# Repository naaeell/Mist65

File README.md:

# Mist65 ⌨✨

Introducing Mist65, a 65% custom keyboard inspired by [bakeneko65](https://github.com/kkatano/bakeneko-65). The PCB, aptly named Mist, features a sleek black design reminiscent of nighttime fog. To keep costs reasonable, the ATmega32u4 controller has been replaced with the budget-friendly RP2040 Zero, maintaining similar functionality.

Designed with a 65% layout, Mist65 strikes a balance between compactness and functionality, housing arrow keys for enhanced usability. VIA support ensures seamless keymap customization to tailor the keyboard to your preferences.

For those interested, the Mist65 PCB is available for purchase [here](https://tokopedia.link/6WUgB6gHmGb) (indonesian domestic). If considering group buy or commercial use, kindly adhere to the specified terms.

For more details about materials, instructions, and other information, please visit this [page](https://github.com/naaeell/Mist65/blob/main/mist65/README.md)

## Features 🔮

- No RGB: Clean and distraction-free experience without RGB lighting.
- Drag and Drop Flashing: Streamlined firmware updates with easy drag-and-drop functionality.
- Staggered Design: Comfortable and ergonomic typing experience with a staggered key layout.
- VIA Support: Extensive keymap customization through VIA support. (Keyboard definition required until VIA branch merge)
- QMK Firmware: Reliable and customizable keyboard experience powered by QMK firmware.
- Cost-Effective Components: Budget-friendly design using readily available components.
- Compact 65% Layout: Perfect balance between size and functionality with arrow keys for convenient navigation.
- RP2040 Zero Controller: Cost-effective and performance-maintaining controller readily available in the market.
- Community-Friendly: Vibrant community of keyboard enthusiasts for sharing experiences and modifications.
- Open-Source Design: Creative and adaptable with an open-source design for user contributions and personalization.

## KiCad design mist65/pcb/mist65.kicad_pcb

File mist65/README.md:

## Materials

Part list
| Name          | Quantity     | Description                |
| :-------------| :----------- | :------------------------- |
| `1N4148`      | `66`         | DO-35 (1N4148 or similar).  |
| `RP2040 Zero` | `1`          | RP2040 Zero (You can use all models, but first pay attention to the pinout). |
| `Kailh hotswap socket (optional)` | `66` | if you want hotswap features and south facing switches. |
| `Mist65 PCB`  | `1`          | Mist65 PCB is available for purchase [here](https://tokopedia.link/6WUgB6gHmGb).|

Case part list

| Name            | Quantity    | Details|
| :---------------| :-----------| :------|
| `Layer 1`       | `1`         | 3mm thicknes.   |
| `Layer 2`       | `3`         | 3mm thickness.   |
| `Layer 3`       | `2`         | 3mm thickness.   |
| `Layer 4`       | `1`         | 1.5mm thickness. |
| `Layer 5`       | `2`         | 3mm thickness.   |
| `bolts and nuts`| `8`         | M2 size with 30mm length.|

*layer 1 is the bottom layer (in order of top).

Tools needed

| Name            | Details      |
| :---------------| :------------|
| `Solder`        |  Any kind of solder is suitable, but I recommend using a pointed or sharp-tipped one.   |
| `Tin`           | You'll need approximately 4-5 meters of tin wire.   |
| `Flux`          | Any type of flux is acceptable, but avoid overusing it.  |
| `Tweezers`      | Opt for tweezers with a hooked shape. |
| `Nail clippers` | Any type with flat surfaces will work.   |

## Let's start building

Firstly, prepare the necessary tools and materials. I will provide you with some tips and tricks. I recommend a soldering temperature of 300 to 350 degrees Celsius; please note that high temperatures can damage the PCB traces. Additionally, the soldering tip may quickly turn black. Each time you solder, ensure to clean the soldering tip thoroughly to prevent residue from sticking to the soldered joints later.

The use of nail clippers instead of cutting pliers is for precision, allowing you to trim component legs more neatly. Before soldering, apply an adequate amount of flux to the PCB. Applying too much flux can complicate cleaning later. Once everything is ready, test-fit the components in place, ensuring they match the silk screen markings on the PCB. Trim any excess component legs promptly; although it may take time, patience is crucial for satisfactory results.

Afterward, solder the components one by one, using tweezers to position them accurately. If a component is tilted, you can correct it with tweezers, but be cautious as this process involves melting the tin and adjusting the component's position. For the microcontroller, there is a ">" sign indicating pin 0 on the rp2040 zero; refer to the picture [below](https://github.com/naaeell/Mist65/blob/main/mist65/pictures/20240113_094051.jpg) for the microcontroller's position. Before soldering, verify that the component placement is correct to achieve neat soldering results.

Begin soldering slowly, ensuring not to melt too much tin; excessive tin can result in poor solder joints. Once all components are soldered, clean the PCB with isopropyl alcohol or contact cleaner.

## Flashing Firmware

- Flash the RPI2040 Zero by pressing and holding the boot button while plugging in the USB until it's detected on the computer as a new drive.

- Drag and drop or copy and paste the file with the .uf2 extension onto the drive. Wait until the keyboard is detected.

#### Unfortunately, the VIA support hasn't been merged into the branch yet. However, to use it, follow these additional steps:

- Visit [https://usevia.app/](https://usevia.app/) and navigate to the gear icon, then enable the "Show Design Tab" option.
- Once active, open the brush icon next to the gear. Click "Load" on the "Load Draft Definition" menu and input the via.json file located in the firmware folder.
- Return to the configuration menu, click on "Device Authorization," and your keyboard will appear, ready to use.

Choose "Mist65_via.uf2" for VIA support or "Mist65_default.uf2" for the default keymap without VIA support.

Create a new keymap tutorial soon!

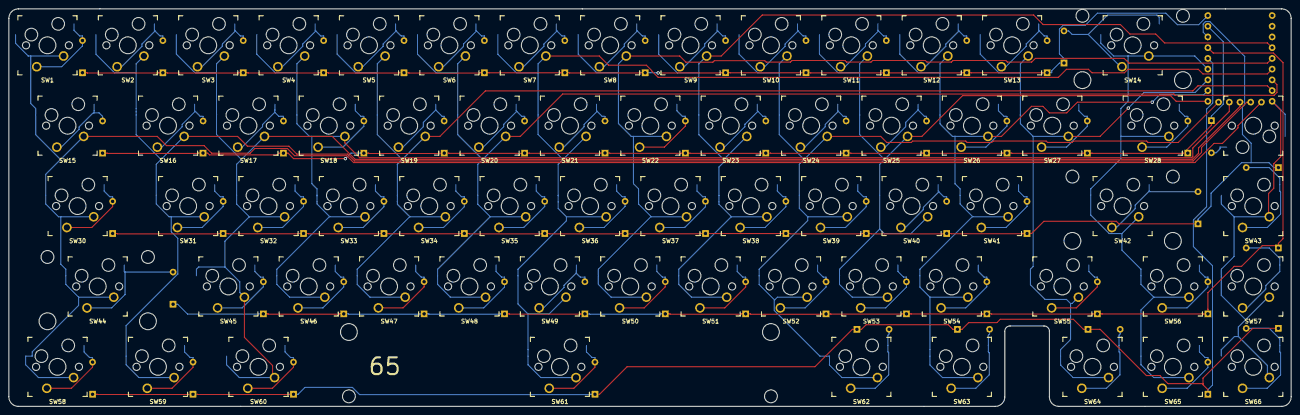
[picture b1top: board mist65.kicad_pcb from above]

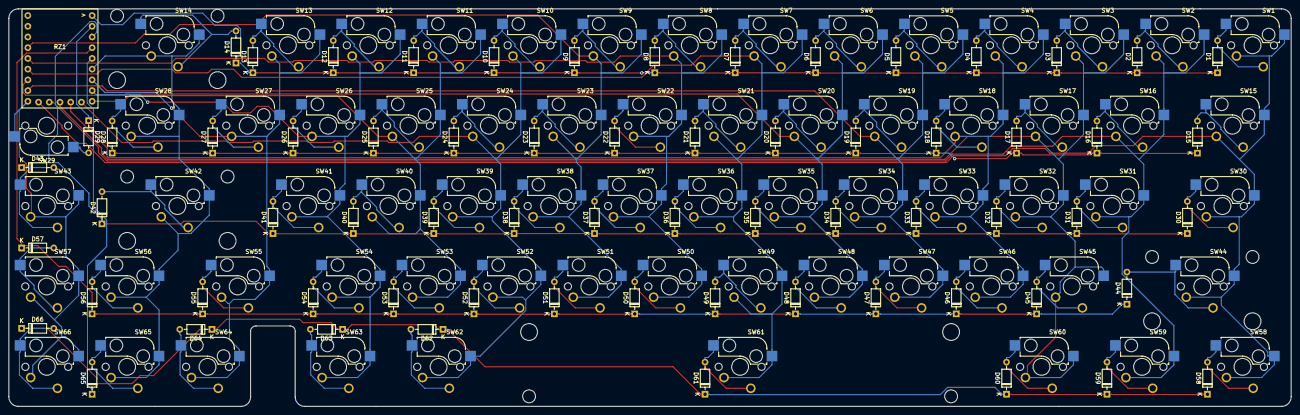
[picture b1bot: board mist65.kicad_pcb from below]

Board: 2 copper layers, 303.9 x 94.2 mm, 137 parts (67 on the bottom side), 86 nets.

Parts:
D1, D2, D3, D4, D5, D6, D7, D8, D9, D10, D11, D12, D13, D14, D15, D16, D17, D18, D19, D20, D21, D22, D23, D24, D25, D26, D27, D28, D29, D30, D31, D32, D33, D34, D35, D36, D37, D38, D39, D40, D41, D42, D43, D44, D45, D46, D47, D48, D49, D50, D51, D52, D53, D54, D55, D56, D57, D58, D59, D60, D61, D62, D63, D64, D65, D66: 1N4148; D_DO-35_SOD27_P7.62mm_Horizontal
RZ1: RP2040-Zero
S1: MX_stab; STAB_MX_6.25u
S2: MX_stab; STAB_MX_2u
S3, S4: MX_stab; STAB_MX_2.25u
SW1, SW2, SW3, SW4, SW5, SW6, SW7, SW8, SW9, SW10, SW11, SW12, SW13, SW16, SW17, SW18, SW19, SW20, SW21, SW22, SW23, SW24, SW25, SW26, SW27, SW31, SW32, SW33, SW34, SW35, SW36, SW37, SW38, SW39, SW40, SW41, SW43, SW45, SW46, SW47, SW48, SW49, SW50, SW51, SW52, SW53, SW54, SW56, SW57, SW64, SW65, SW66: 1u; Kailh_socket_MX_optional
SW14: 2u; Kailh_socket_MX_optional
SW15, SW28: 1.5u; Kailh_socket_MX_optional
SW29: 1u; Kailh_socket_MX
SW30, SW55: 1.75u; Kailh_socket_MX_optional
SW42, SW44: 2.25u; Kailh_socket_MX_optional
SW58, SW59, SW60, SW62, SW63: 1.25u; Kailh_socket_MX_optional
SW61: 6.25u; Kailh_socket_MX_optional

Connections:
COL0: RZ1.14 (GP13), SW1.2 (B), SW15.2 (B), SW30.2 (B), SW44.2 (B), SW58.2 (B)
COL1: RZ1.13 (GP12), SW2.2 (B), SW16.2 (B), SW31.2 (B), SW59.2 (B)
COL2: RZ1.12 (GP11), SW3.2 (B), SW17.2 (B), SW32.2 (B), SW45.2 (B), SW60.2 (B)
COL3: RZ1.11 (GP10), SW4.2 (B), SW18.2 (B), SW33.2 (B), SW46.2 (B)
COL4: RZ1.16 (GP15), SW5.2 (B), SW19.2 (B), SW34.2 (B), SW47.2 (B)
COL5: RZ1.17 (GP26), SW6.2 (B), SW20.2 (B), SW35.2 (B), SW48.2 (B)
COL6: RZ1.18 (GP27), SW7.2 (B), SW21.2 (B), SW36.2 (B), SW49.2 (B), SW61.2 (B)
COL7: RZ1.19 (GP28), SW8.2 (B), SW22.2 (B), SW37.2 (B), SW50.2 (B)
COL8: RZ1.20 (GP29), SW9.2 (B), SW23.2 (B), SW38.2 (B), SW51.2 (B)
COL9: RZ1.10 (GP9), SW10.2 (B), SW24.2 (B), SW39.2 (B), SW52.2 (B), SW62.2 (B)
COL10: RZ1.9 (GP8), SW11.2 (B), SW25.2 (B), SW40.2 (B), SW53.2 (B)
COL11: RZ1.8 (GP7), SW12.2 (B), SW26.2 (B), SW41.2 (B), SW54.2 (B), SW63.2 (B)
COL12: RZ1.7 (GP6), SW13.2 (B), SW27.2 (B), SW55.2 (B), SW64.2 (B)
COL13: RZ1.6 (GP5), SW14.2 (B), SW28.2 (B), SW42.2 (B), SW56.2 (B), SW65.2 (B)
COL14: RZ1.15 (GP14), SW29.2 (B), SW43.2 (B), SW57.2 (B), SW66.2 (B)
unnamed: D1.2 (A), SW1.1 (A)
unnamed: D2.2 (A), SW2.1 (A)
unnamed: D3.2 (A), SW3.1 (A)
unnamed: D4.2 (A), SW4.1 (A)
unnamed: D5.2 (A), SW5.1 (A)
unnamed: D6.2 (A), SW6.1 (A)
unnamed: D7.2 (A), SW7.1 (A)
unnamed: D8.2 (A), SW8.1 (A)
unnamed: D9.2 (A), SW9.1 (A)
unnamed: D10.2 (A), SW10.1 (A)
unnamed: D11.2 (A), SW11.1 (A)
unnamed: D12.2 (A), SW12.1 (A)
unnamed: D13.2 (A), SW13.1 (A)
unnamed: D14.2 (A), SW14.1 (A)
unnamed: D15.2 (A), SW15.1 (A)
unnamed: D16.2 (A), SW16.1 (A)
unnamed: D17.2 (A), SW17.1 (A)
unnamed: D18.2 (A), SW18.1 (A)
unnamed: D19.2 (A), SW19.1 (A)
unnamed: D20.2 (A), SW20.1 (A)
unnamed: D21.2 (A), SW21.1 (A)
unnamed: D22.2 (A), SW22.1 (A)
unnamed: D23.2 (A), SW23.1 (A)
unnamed: D24.2 (A), SW24.1 (A)
unnamed: D25.2 (A), SW25.1 (A)
unnamed: D26.2 (A), SW26.1 (A)
unnamed: D27.2 (A), SW27.1 (A)
unnamed: D28.2 (A), SW28.1 (A)
unnamed: D29.2 (A), SW29.1 (A)
unnamed: D30.2 (A), SW30.1 (A)
unnamed: D31.2 (A), SW31.1 (A)
unnamed: D32.2 (A), SW32.1 (A)
unnamed: D33.2 (A), SW33.1 (A)
unnamed: D34.2 (A), SW34.1 (A)
unnamed: D35.2 (A), SW35.1 (A)
unnamed: D36.2 (A), SW36.1 (A)
unnamed: D37.2 (A), SW37.1 (A)
unnamed: D38.2 (A), SW38.1 (A)
unnamed: D39.2 (A), SW39.1 (A)
unnamed: D40.2 (A), SW40.1 (A)
unnamed: D41.2 (A), SW41.1 (A)
unnamed: D42.2 (A), SW42.1 (A)
unnamed: D43.2 (A), SW43.1 (A)
unnamed: D44.2 (A), SW44.1 (A)
unnamed: D45.2 (A), SW45.1 (A)
unnamed: D46.2 (A), SW46.1 (A)
unnamed: D47.2 (A), SW47.1 (A)
unnamed: D48.2 (A), SW48.1 (A)
unnamed: D49.2 (A), SW49.1 (A)
unnamed: D50.2 (A), SW50.1 (A)
unnamed: D51.2 (A), SW51.1 (A)
unnamed: D52.2 (A), SW52.1 (A)
unnamed: D53.2 (A), SW53.1 (A)
unnamed: D54.2 (A), SW54.1 (A)
unnamed: D55.2 (A), SW55.1 (A)
unnamed: D56.2 (A), SW56.1 (A)
unnamed: D57.2 (A), SW57.1 (A)
unnamed: D58.2 (A), SW58.1 (A)
unnamed: D59.2 (A), SW59.1 (A)
unnamed: D60.2 (A), SW60.1 (A)
unnamed: D61.2 (A), SW61.1 (A)
unnamed: D62.2 (A), SW62.1 (A)
unnamed: D63.2 (A), SW63.1 (A)
unnamed: D64.2 (A), SW64.1 (A)
unnamed: D65.2 (A), SW65.1 (A)
unnamed: D66.2 (A), SW66.1 (A)
ROW0: D1.1 (K), D2.1 (K), D3.1 (K), D4.1 (K), D5.1 (K), D6.1 (K), D7.1 (K), D8.1 (K), D9.1 (K), D10.1 (K), D11.1 (K), D12.1 (K), D13.1 (K), D14.1 (K), RZ1.1 (GP0)
ROW1: D15.1 (K), D16.1 (K), D17.1 (K), D18.1 (K), D19.1 (K), D20.1 (K), D21.1 (K), D22.1 (K), D23.1 (K), D24.1 (K), D25.1 (K), D26.1 (K), D27.1 (K), D28.1 (K), D29.1 (K), RZ1.2 (GP1)
ROW2: D30.1 (K), D31.1 (K), D32.1 (K), D33.1 (K), D34.1 (K), D35.1 (K), D36.1 (K), D37.1 (K), D38.1 (K), D39.1 (K), D40.1 (K), D41.1 (K), D42.1 (K), D43.1 (K), RZ1.3 (GP2)
ROW3: D44.1 (K), D45.1 (K), D46.1 (K), D47.1 (K), D48.1 (K), D49.1 (K), D50.1 (K), D51.1 (K), D52.1 (K), D53.1 (K), D54.1 (K), D55.1 (K), D56.1 (K), D57.1 (K), RZ1.4 (GP3)
ROW4: D58.1 (K), D59.1 (K), D60.1 (K), D61.1 (K), D62.1 (K), D63.1 (K), D64.1 (K), D65.1 (K), D66.1 (K), RZ1.5 (GP4)

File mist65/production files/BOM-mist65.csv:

Comment,Designator,Footprint,LCSC
1N4148,"D1,D10,D11,D12,D13,D14,D15,D16,D17,D18,D19,D2,D20,D21,D22,D23,D24,D25,D26,D27,D28,D29,D3,D30,D31,D32,D33,D34,D35,D36,D37,D38,D39,D4,D40,D41,D42,D43,D44,D45,D46,D47,D48,D49,D5,D50,D51,D52,D53,D54,D55,D56,D57,D58,D59,D6,D60,D61,D62,D63,D64,D65,D66,D7,D8,D9",D_DO-35_SOD27_P7.62mm_Horizontal,C81598
1u,SW53,Kailh_socket_MX_optional,
1u,SW25,Kailh_socket_MX_optional,
1u,SW16,Kailh_socket_MX_optional,
1u,SW21,Kailh_socket_MX_optional,
1u,SW37,Kailh_socket_MX_optional,
1u,SW5,Kailh_socket_MX_optional,
1u,SW33,Kailh_socket_MX_optional,
1u,SW13,Kailh_socket_MX_optional,
1u,SW10,Kailh_socket_MX_optional,
1.25u,SW63,Kailh_socket_MX_optional,
1u,SW18,Kailh_socket_MX_optional,
1u,SW52,Kailh_socket_MX_optional,
1u,SW56,Kailh_socket_MX_optional,
1u,SW45,Kailh_socket_MX_optional,
1u,SW43,Kailh_socket_MX_optional,
1.25u,SW62,Kailh_socket_MX_optional,
1u,SW29,Kailh_socket_MX,
1u,SW36,Kailh_socket_MX_optional,
2.25u,SW42,Kailh_socket_MX_optional,
1u,SW27,Kailh_socket_MX_optional,
1u,SW2,Kailh_socket_MX_optional,
1u,SW35,Kailh_socket_MX_optional,
1u,SW31,Kailh_socket_MX_optional,
MX_stab,S4,STAB_MX_2.25u,
1u,SW41,Kailh_socket_MX_optional,
1u,SW49,Kailh_socket_MX_optional,
1u,SW12,Kailh_socket_MX_optional,
1u,SW54,Kailh_socket_MX_optional,
1.5u,SW28,Kailh_socket_MX_optional,
1u,SW17,Kailh_socket_MX_optional,
1u,SW24,Kailh_socket_MX_optional,
1u,SW64,Kailh_socket_MX_optional,
MX_stab,S2,STAB_MX_2u,
1.5u,SW15,Kailh_socket_MX_optional,
1u,SW66,Kailh_socket_MX_optional,
1u,SW65,Kailh_socket_MX_optional,
2.25u,SW44,Kailh_socket_MX_optional,
1u,SW26,Kailh_socket_MX_optional,
1u,SW19,Kailh_socket_MX_optional,
MX_stab,S3,STAB_MX_2.25u,
1u,SW6,Kailh_socket_MX_optional,
1u,SW3,Kailh_socket_MX_optional,
1u,SW48,Kailh_socket_MX_optional,
1u,SW32,Kailh_socket_MX_optional,
1u,SW20,Kailh_socket_MX_optional,
6.25u,SW61,Kailh_socket_MX_optional,
1u,SW57,Kailh_socket_MX_optional,
2u,SW14,Kailh_socket_MX_optional,
1.25u,SW59,Kailh_socket_MX_optional,
1u,SW34,Kailh_socket_MX_optional,
1.75u,SW30,Kailh_socket_MX_optional,
1u,SW23,Kailh_socket_MX_optional,
1u,SW11,Kailh_socket_MX_optional,
1u,SW1,Kailh_socket_MX_optional,
1.75u,SW55,Kailh_socket_MX_optional,
1u,SW39,Kailh_socket_MX_optional,
1u,SW40,Kailh_socket_MX_optional,
1u,SW22,Kailh_socket_MX_optional,
1u,SW9,Kailh_socket_MX_optional,
1u,SW50,Kailh_socket_MX_optional,
1u,SW4,Kailh_socket_MX_optional,
1.25u,SW58,Kailh_socket_MX_optional,
1u,SW46,Kailh_socket_MX_optional,
MX_stab,S1,STAB_MX_6.25u,
1u,SW38,Kailh_socket_MX_optional,
1u,SW8,Kailh_socket_MX_optional,
1u,SW51,Kailh_socket_MX_optional,
1.25u,SW60,Kailh_socket_MX_optional,
1u,SW7,Kailh_socket_MX_optional,
1u,SW47,Kailh_socket_MX_optional,
RP2040-Zero,RZ1,RP2040-Zero,

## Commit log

2024-01-14 Rename README (1).md to README.md
